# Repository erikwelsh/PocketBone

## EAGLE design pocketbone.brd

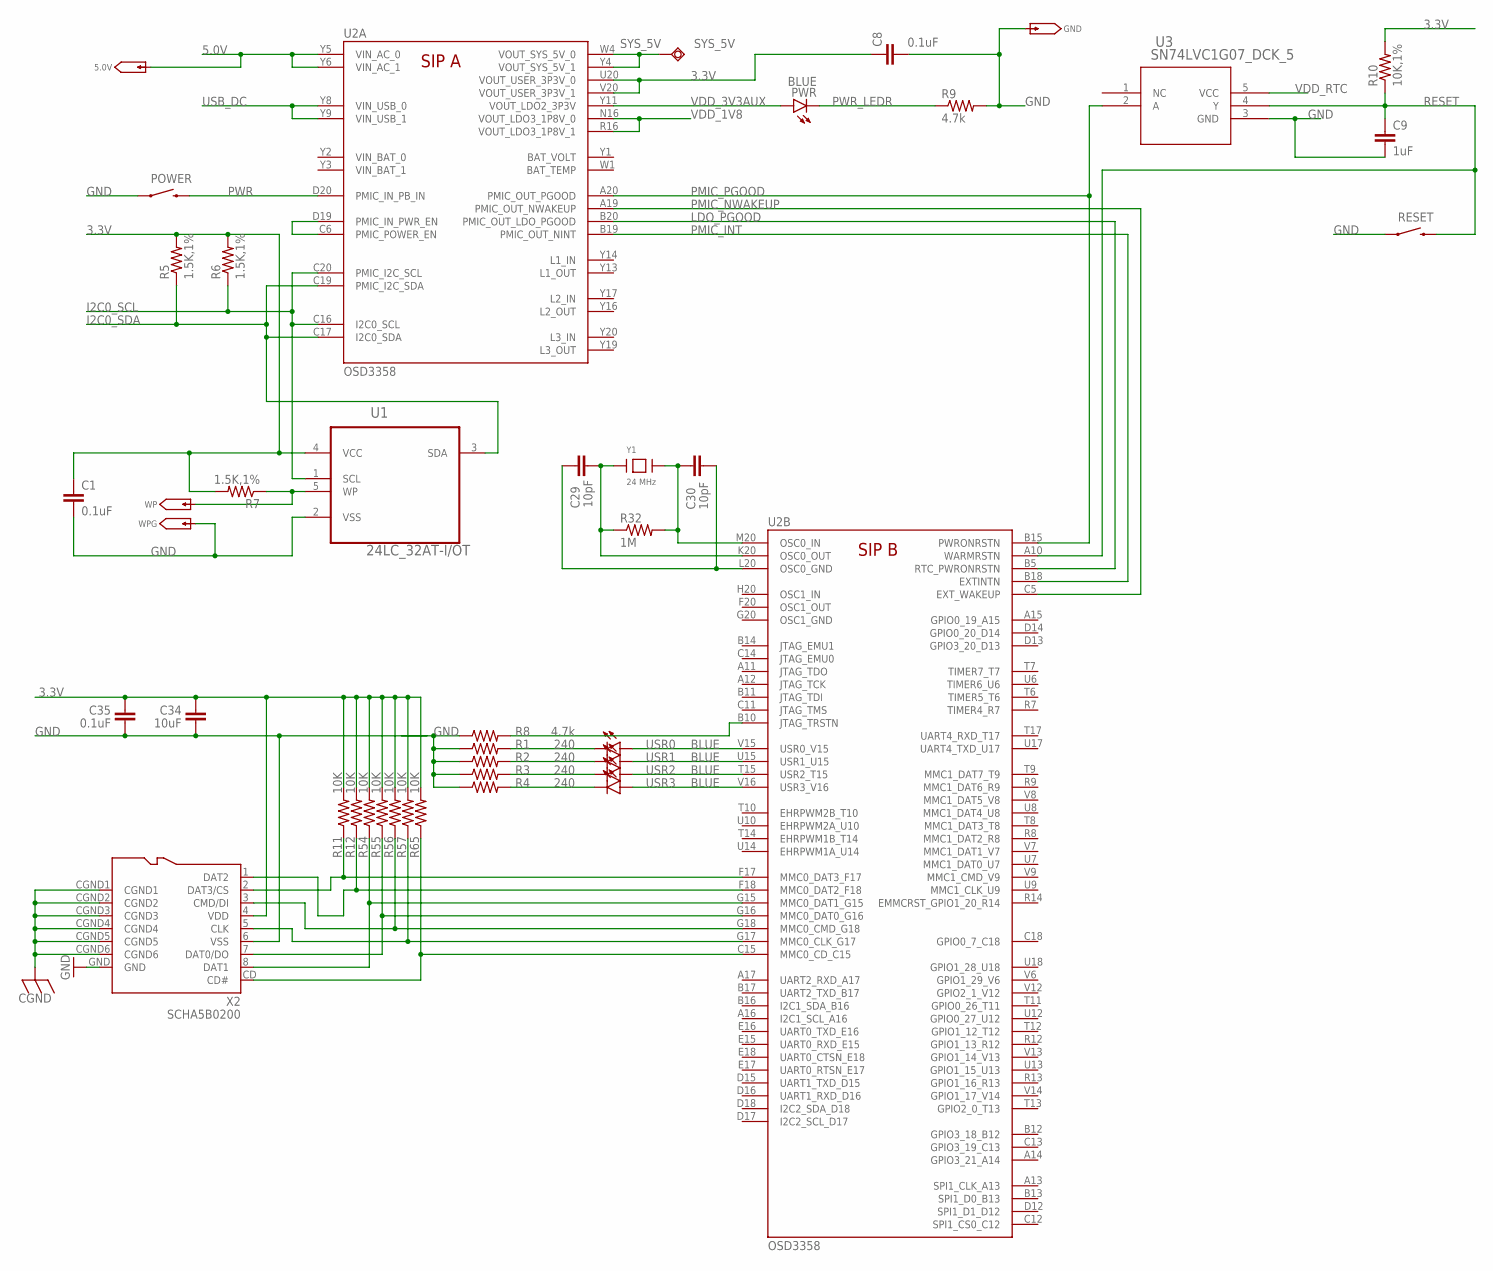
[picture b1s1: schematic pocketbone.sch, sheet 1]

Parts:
5.0V: GHI_TESTPAD/W_HOLE_1X1; GHI2_TESTPAD/W_HOLE_1X1
C1, C8, C35: 0.1uF; 0402-CAP
C9: 1uF; 0402-CAP
C29, C30: 10pF; 0402-CAP
C34: 10uF; 0805
GND: GHI_TESTPAD/W_HOLE_1X1; GHI2_TESTPAD/W_HOLE_1X1
POWER: SWITCH-MOMENTARY-2SMD-1101NE; TACTILE-SWITCH-1101NE
PWR: BLUE; LED-0603
R1, R2, R3, R4: 240; 0402-RES
R5, R6, R7: 1.5K,1%; 0402-RES
R8, R9: 4.7k; 0402-RES
R10: 10K,1%; 0402-RES
R11, R12, R54, R55, R56, R57, R65: 10K; 0402-RES
R32: 1M; 0402-RES
RESET: SWITCH-MOMENTARY-2SMD-1101NE; TACTILE-SWITCH-1101NE
SYS_5V: TPSQB1,27; B1,27
U1: 24LC_32AT-I/OT; SOT95P290X145-5N
U2: OSD3358
U3: SN74LVC1G07_DCK_5; DCK5
USR0, USR1, USR2, USR3: BLUE; LED-0603
WP: GHI_TESTPAD/W_HOLE_1X1; GHI2_TESTPAD/W_HOLE_1X1
WPG: GHI_TESTPAD/W_HOLE_1X1; GHI2_TESTPAD/W_HOLE_1X1
X2: SCHA5B0200
Y1: 24 MHz; CRYSTAL_5X3.2MM

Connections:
3.3V: C1.1, C8.1, C34.2, C35.2, R5.2, R6.2, R7.2, R10.2, R11.2, R12.2, R54.2, R55.2, R56.2, R57.2, R65.2, U1.4 (VCC), U2.U20 (VOUT_USER_3P3V_0), U2.V20 (VOUT_USER_3P3V_1), X2.4 (VDD); also elsewhere on the board
5.0V: 5.0V.P$1, U2.Y5 (VIN_AC_0), U2.Y6 (VIN_AC_1); also elsewhere on the board
CGND: X2.CGND1, X2.CGND2, X2.CGND3, X2.CGND4, X2.CGND5, X2.CGND6; also elsewhere on the board
GND: C1.2, C8.2, C9.2, C34.1, C35.1, GND.P$1, POWER.1, R1.1, R2.1, R3.1, R4.1, R8.1, R9.2, RESET.1, U1.2 (VSS), U3.3 (GND), WPG.P$1, X2.6 (VSS), X2.GND; also elsewhere on the board
I2C0_SCL: R6.1, U1.1 (SCL), U2.C16 (I2C0_SCL), U2.C20 (PMIC_I2C_SCL)
I2C0_SDA: R5.1, U1.3 (SDA), U2.C17 (I2C0_SDA), U2.C19 (PMIC_I2C_SDA)
LDO_PGOOD: U2.B5 (RTC_PWRONRSTN), U2.B20 (PMIC_OUT_LDO_PGOOD)
unnamed: R56.1, U2.G18 (MMC0_CMD_G18), X2.3 (CMD/DI)
unnamed: R55.1, U2.G16 (MMC0_DAT0_G16), X2.7 (DAT0/DO)
unnamed: R54.1, U2.G15 (MMC0_DAT1_G15), X2.8 (DAT1)
unnamed: R65.1, U2.C15 (MMC0_CD_C15), X2.CD (CD#)
unnamed: R57.1, U2.G17 (MMC0_CLK_G17), X2.5 (CLK)
unnamed: R11.1, U2.F17 (MMC0_DAT3_F17), X2.2 (DAT3/CS)
unnamed: U2.C6 (PMIC_POWER_EN), U2.D19 (PMIC_IN_PWR_EN)
unnamed: C30.1, R32.2, U2.M20 (OSC0_IN), Y1.2
unnamed: C29.1, R32.1, U2.K20 (OSC0_OUT), Y1.1
unnamed: R7.1, U1.5 (WP), WP.P$1
unnamed: C29.2, C30.2, U2.L20 (OSC0_GND)
unnamed: R8.2, U2.B10 (JTAG_TRSTN)
unnamed: U2.V16 (USR3_V16), USR3.A
unnamed: U2.T15 (USR2_T15), USR2.A
unnamed: U2.U15 (USR1_U15), USR1.A
unnamed: U2.V15 (USR0_V15), USR0.A
unnamed: R1.2, USR0.C
unnamed: R2.2, USR1.C
unnamed: R3.2, USR2.C
unnamed: R4.2, USR3.C
NTE1: R12.1, U2.F18 (MMC0_DAT2_F18), X2.1 (DAT2)
PMIC_INT: U2.B18 (EXTINTN), U2.B19 (PMIC_OUT_NINT)
PMIC_NWAKEUP: U2.A19 (PMIC_OUT_NWAKEUP), U2.C5 (EXT_WAKEUP)
PMIC_PGOOD: U2.A20 (PMIC_OUT_PGOOD), U2.B15 (PWRONRSTN), U3.2 (A)
PWR: POWER.2, U2.D20 (PMIC_IN_PB_IN)
PWR_LEDR: PWR.C, R9.1
RESET: C9.1, R10.1, RESET.2, U2.A10 (WARMRSTN), U3.4 (Y)
SYS_5V: SYS_5V.TP, U2.W4 (VOUT_SYS_5V_0), U2.Y4 (VOUT_SYS_5V_1); also elsewhere on the board
USB_DC: U2.Y8 (VIN_USB_0), U2.Y9 (VIN_USB_1); also elsewhere on the board
VDD_1V8: U2.N16 (VOUT_LDO3_1P8V_0), U2.R16 (VOUT_LDO3_1P8V_1); also elsewhere on the board
VDD_3V3AUX: PWR.A, U2.Y11 (VOUT_LDO2_3P3V)
VDD_RTC: U3.5 (VCC); also elsewhere on the board
VIN_BAT_0: U2.Y2 (VIN_BAT_0)
VIN_BAT_1: U2.Y3 (VIN_BAT_1)

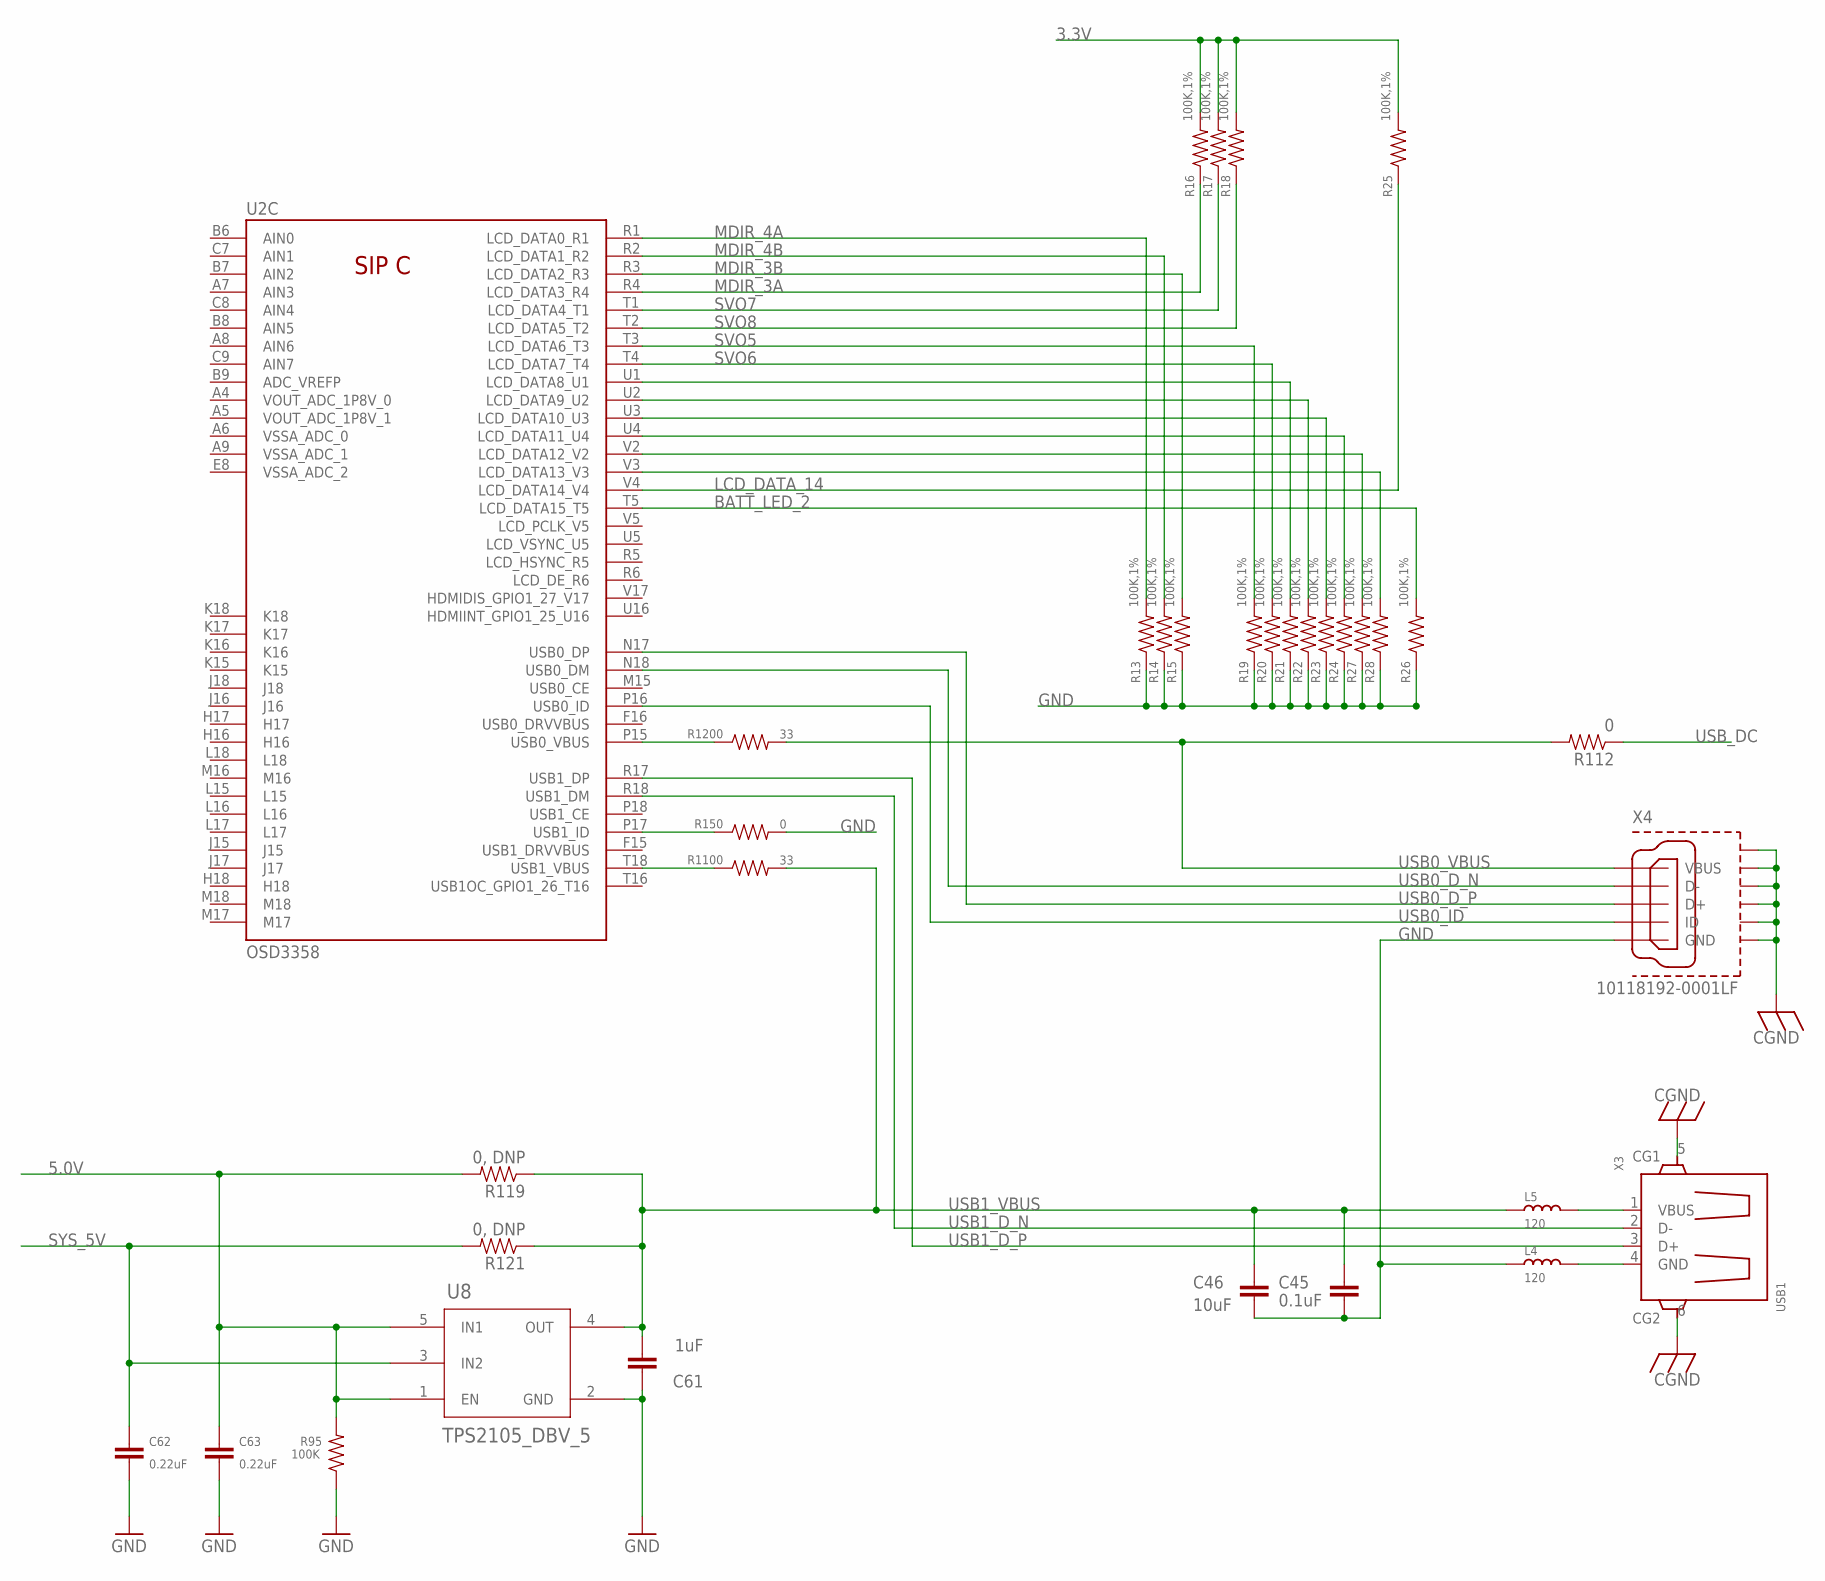
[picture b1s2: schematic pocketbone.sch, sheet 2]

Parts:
C45: 0.1uF; 0402-CAP
C46: 10uF; 0805
C61: 1uF; 0402-CAP
C62, C63: 0.22uF; 0402-CAP
L4, L5: 120; L0603
R13, R14, R15, R16, R17, R18, R19, R20, R21, R22, R23, R24, R25, R26, R27, R28: 100K,1%; 0402-RES
R95: 100K; 0402-RES
R112: 0; 0603-RES
R119, R121: 0, DNP; 0603-RES
R150: 0; 0402-RES
R1100, R1200: 33; 0402-RES
U2: OSD3358
U8: TPS2105_DBV_5; DBV5
X3: USB1; USB_HOST_HORIZONTAL_W/CHASSIS_GND
X4: 10118192-0001LF; 10118192-0001LF(MICRO-USB-B-AMPHENOL-FCI)

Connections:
3.3V: R16.2, R17.2, R18.2, R25.2; also elsewhere on the board
5.0V: C63.1, R95.2, R119.2, U8.1 (EN), U8.5 (IN1); also elsewhere on the board
BATT_LED_2: R26.2, U2.T5 (LCD_DATA15_T5)
CGND: X3.5 (CG1), X3.6 (CG2), X4.CGND1 (SGND1), X4.CGND2 (SGND2), X4.CGND3 (SGND3), X4.CGND4 (SGND4), X4.CGND5 (SGND5), X4.CGND6 (SGND6); also elsewhere on the board
EQEP_1A: R27.2, U2.V2 (LCD_DATA12_V2)
EQEP_1B: R28.2, U2.V3 (LCD_DATA13_V3)
GND: C45.2, C46.2, C61.1, C62.2, C63.2, L4.1, R13.1, R14.1, R15.1, R19.1, R20.1, R21.1, R22.1, R23.1, R24.1, R26.1, R27.1, R28.1, R95.1, R150.2, U8.2 (GND), X4.GND; also elsewhere on the board
LCD_DATA_14: R25.1, U2.V4 (LCD_DATA14_V4)
MDIR_2B: R24.2, U2.U4 (LCD_DATA11_U4)
MDIR_3A: R16.1, U2.R4 (LCD_DATA3_R4)
MDIR_3B: R15.2, U2.R3 (LCD_DATA2_R3)
MDIR_4A: R13.2, U2.R1 (LCD_DATA0_R1)
MDIR_4B: R14.2, U2.R2 (LCD_DATA1_R2)
unnamed: R1200.1, U2.P15 (USB0_VBUS)
unnamed: R1100.1, U2.T18 (USB1_VBUS)
unnamed: R150.1, U2.P17 (USB1_ID)
unnamed: L4.2, X3.4 (GND)
unnamed: L5.2, X3.1 (VBUS)
SERVO_EN: R23.2, U2.U3 (LCD_DATA10_U3)
SVO5: R19.2, U2.T3 (LCD_DATA6_T3)
SVO6: R20.2, U2.T4 (LCD_DATA7_T4)
SVO7: R17.1, U2.T1 (LCD_DATA4_T1)
SVO8: R18.1, U2.T2 (LCD_DATA5_T2)
SYS_5V: C62.1, R121.2, U8.3 (IN2); also elsewhere on the board
UART5_RX: R22.2, U2.U2 (LCD_DATA9_U2)
UART5_TX: R21.2, U2.U1 (LCD_DATA8_U1)
USB0_D_N: U2.N18 (USB0_DM), X4.D-
USB0_D_P: U2.N17 (USB0_DP), X4.D+
USB0_ID: U2.P16 (USB0_ID), X4.ID
USB0_VBUS: R112.2, R1200.2, X4.VBUS
USB1_D_N: U2.R18 (USB1_DM), X3.2 (D-)
USB1_D_P: U2.R17 (USB1_DP), X3.3 (D+)
USB1_VBUS: C45.1, C46.1, C61.2, L5.1, R119.1, R121.1, R1100.2, U8.4 (OUT)
USB_DC: R112.1; also elsewhere on the board
VIN_BAT_0: U2.Y2 (VIN_BAT_0)
VIN_BAT_1: U2.Y3 (VIN_BAT_1)

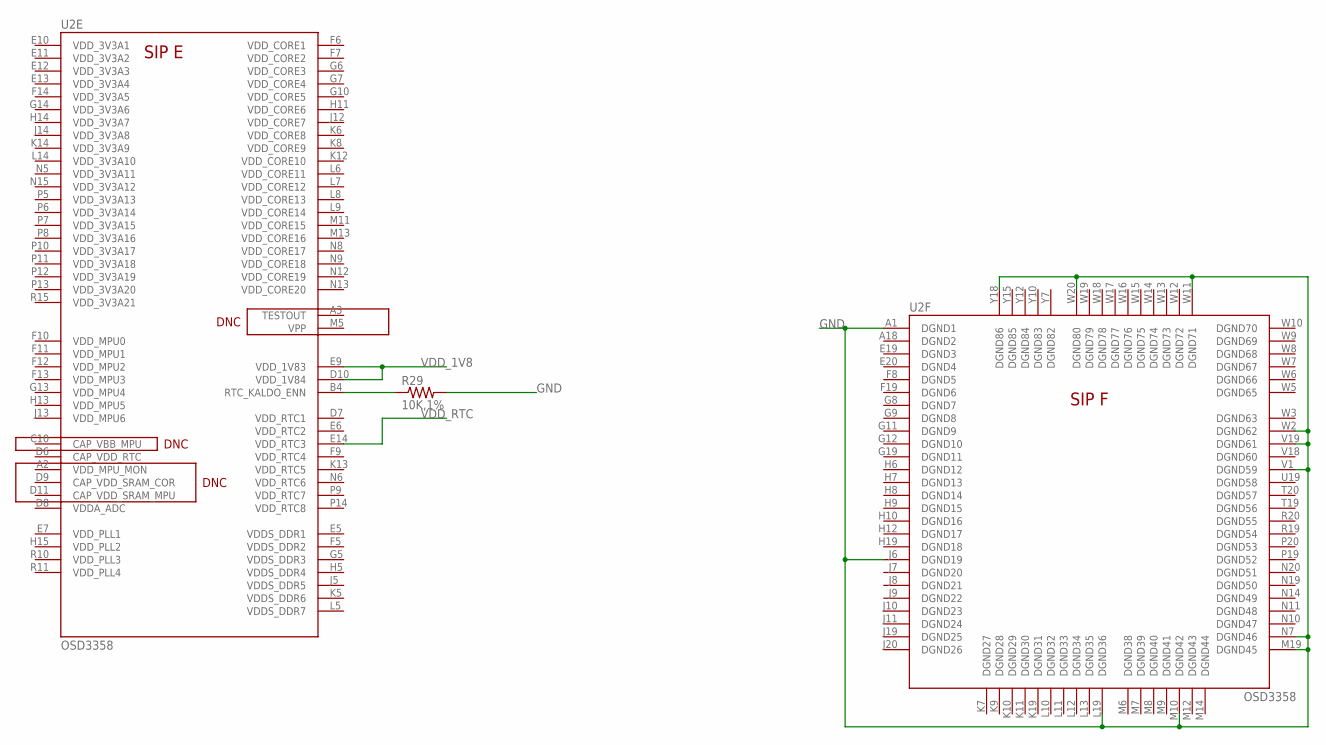
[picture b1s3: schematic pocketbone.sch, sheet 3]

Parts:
R29: 10K,1%; 0402-RES
U2: OSD3358

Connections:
GND: R29.2, U2.A1 (DGND1), U2.J6 (DGND19), U2.L19 (DGND36), U2.M10 (DGND42), U2.M19 (DGND45), U2.N7 (DGND46), U2.V1 (DGND59), U2.V19 (DGND61), U2.W2 (DGND62), U2.W11 (DGND71), U2.W20 (DGND80), U2.Y18 (DGND86); also elsewhere on the board
unnamed: R29.1, U2.B4 (RTC_KALDO_ENN)
VDD_1V8: U2.D10 (VDD_1V84), U2.E9 (VDD_1V83); also elsewhere on the board
VDD_RTC: U2.E14 (VDD_RTC3); also elsewhere on the board
VIN_BAT_0: U2.Y2 (VIN_BAT_0)
VIN_BAT_1: U2.Y3 (VIN_BAT_1)

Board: 2 copper layers, 76 parts (2 on the bottom side), 68 nets, no tracks yet.

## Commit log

2016-11-22 Updated components to match BB Blue.

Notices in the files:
parts and their libraries:
SparkFun-Electromechanical: Licensing: Creative Commons ShareAlike 4.0 International - https://creativecommons.org/licenses/by-sa/4.0
SparkFun-Resistors: Licensing: CC v3.0 Share-Alike You are welcome to use this library for commercial purposes.
